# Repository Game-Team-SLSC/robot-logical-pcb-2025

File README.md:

# Game Team's robot pcb for Eurobot Junior 2025

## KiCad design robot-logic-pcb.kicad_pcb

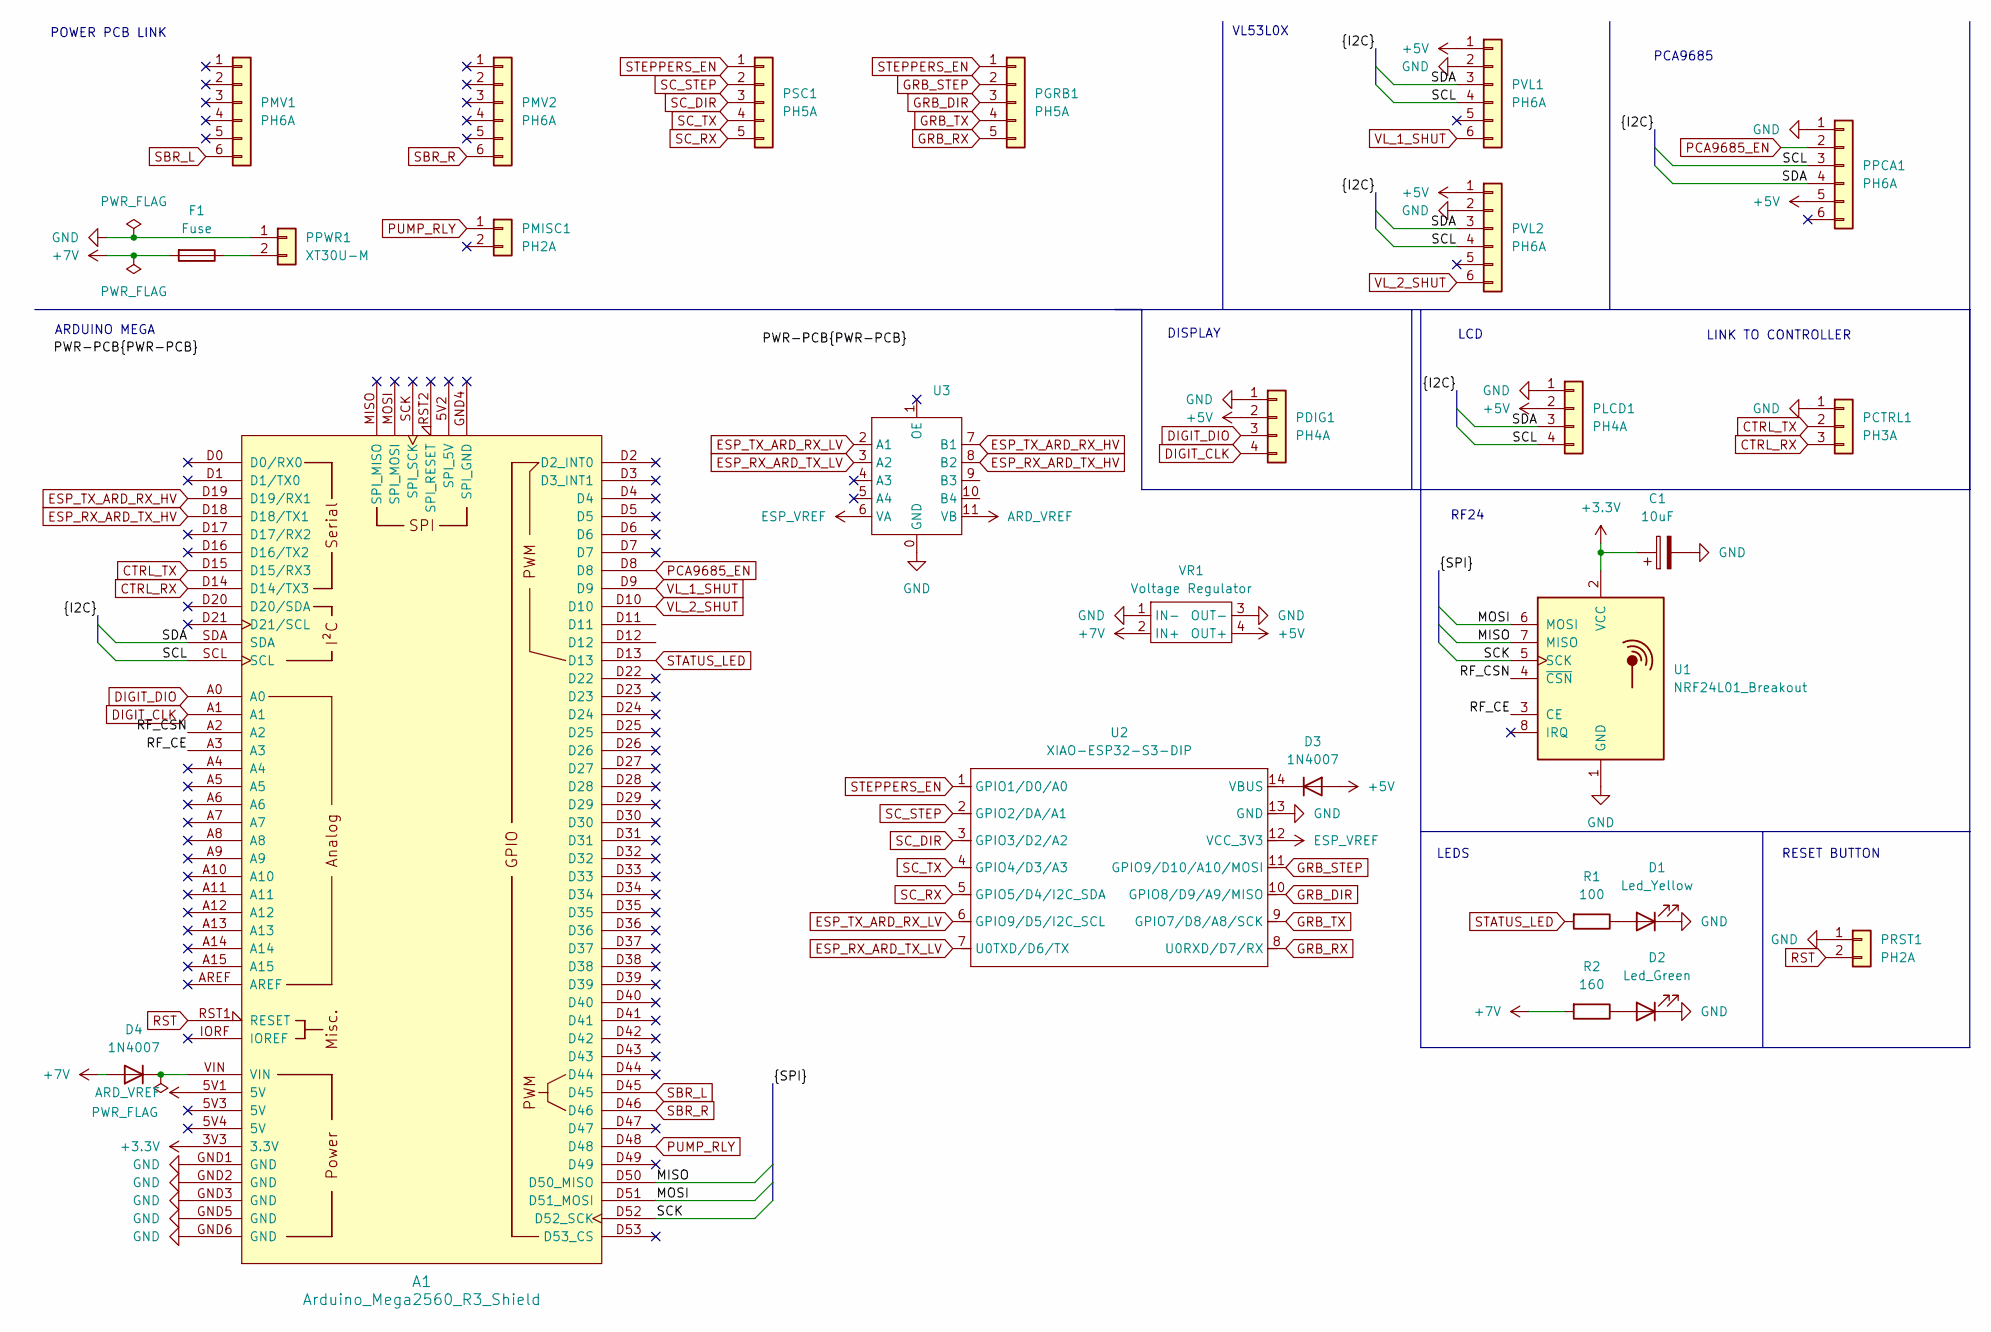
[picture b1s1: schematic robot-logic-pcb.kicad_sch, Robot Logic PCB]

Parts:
A1: Arduino_Mega2560_R3_Shield
C1: 10uF; CP_Radial_D5.0mm_P2.00mm
D1: Led_Yellow; LED_D5.0mm
D2: Led_Green; LED_D5.0mm
D3, D4: 1N4007; D_DO-41_SOD81_P2.54mm_Vertical_AnodeUp
F1: Fuse; Fuseholder_Cylinder-5x20mm_Schurter_0031_8201_Horizontal_Op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
PCTRL1: PH3A; JST_PH_B3B-PH-K_1x03_P2.00mm_Vertical
PDIG1: PH4A; JST_PH_B4B-PH-K_1x04_P2.00mm_Vertical
PGRB1: PH5A; JST_PH_B5B-PH-K_1x05_P2.00mm_Vertical
PLCD1: PH4A; JST_PH_B4B-PH-K_1x04_P2.00mm_Vertical
PMISC1: PH2A; JST_PH_B2B-PH-K_1x02_P2.00mm_Vertical
PMV1, PMV2: PH6A; JST_PH_B6B-PH-K_1x06_P2.00mm_Vertical
PPCA1: PH6A; JST_PH_B6B-PH-K_1x06_P2.00mm_Vertical
PPWR1: XT30U-M; AMASS_XT30U-M_1x02_P5.0mm_Vertical
PRST1: PH2A; JST_PH_B2B-PH-K_1x02_P2.00mm_Vertical
PSC1: PH5A; JST_PH_B5B-PH-K_1x05_P2.00mm_Vertical
PVL1, PVL2: PH6A; JST_PH_B6B-PH-K_1x06_P2.00mm_Vertical
R1: 100; R_Axial_DIN0207_L6.3mm_D2.5mm_P7.62mm_Horizontal
R2: 160; R_Axial_DIN0207_L6.3mm_D2.5mm_P7.62mm_Horizontal
U1: NRF24L01_Breakout; nRF24L01_Breakout
U2: XIAO-ESP32-S3-DIP; XIAO-ESP32S3-DIP
U3: TXB0104-BREAKOUT
VR1: Voltage Regulator; MP1584EN

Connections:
+3.3V: A1.3V3 (3.3V), C1.1, U1.2 (VCC)
+5V: D3.2 (A), PDIG1.2, PLCD1.2, PPCA1.5, PVL1.1, PVL2.1, VR1.4 (OUT+)
+7V: D4.2 (A), F1.2, R2.2, VR1.2 (IN+)
/MISO: A1.D50 (D50_MISO), U1.7 (MISO)
/MOSI: A1.D51 (D51_MOSI), U1.6 (MOSI)
/RF_CE: A1.A3, U1.3 (CE)
/RF_CSN: A1.A2, U1.4 (~CSN)
/SCK: A1.D52 (D52_SCK), U1.5 (SCK)
/SCL: A1.SCL, PLCD1.4, PPCA1.3, PVL1.4, PVL2.4
/SDA: A1.SDA, PLCD1.3, PPCA1.4, PVL1.3, PVL2.3
ARD_VREF: A1.5V1 (5V), U3.11 (VB)
CTRL_RX: A1.D14 (D14/TX3), PCTRL1.3
CTRL_TX: A1.D15 (D15/RX3), PCTRL1.2
DIGIT_CLK: A1.A1, PDIG1.4
DIGIT_DIO: A1.A0, PDIG1.3
ESP_RX_ARD_TX_HV: A1.D18 (D18/TX1), U3.8 (B2)
ESP_RX_ARD_TX_LV: U2.7 (U0TXD/D6/TX), U3.3 (A2)
ESP_TX_ARD_RX_HV: A1.D19 (D19/RX1), U3.7 (B1)
ESP_TX_ARD_RX_LV: U2.6 (GPIO9/D5/I2C_SCL), U3.2 (A1)
ESP_VREF: U2.12 (VCC_3V3), U3.6 (VA)
GND: A1.GND1 (GND), A1.GND2 (GND), A1.GND3 (GND), A1.GND5 (GND), A1.GND6 (GND), C1.2, D1.1 (K), D2.1 (K), PCTRL1.1, PDIG1.1, PLCD1.1, PPCA1.1, PPWR1.1, PRST1.1, PVL1.2, PVL2.2, U1.1 (GND), U2.13 (GND), U3.0 (GND), VR1.1 (IN-), VR1.3 (OUT-)
GRB_DIR: PGRB1.3, U2.10 (GPIO8/D9/A9/MISO)
GRB_RX: PGRB1.5, U2.8 (U0RXD/D7/RX)
GRB_STEP: PGRB1.2, U2.11 (GPIO9/D10/A10/MOSI)
GRB_TX: PGRB1.4, U2.9 (GPIO7/D8/A8/SCK)
unnamed: D1.2 (A), R1.1
unnamed: D2.2 (A), R2.1
unnamed: D3.1 (K), U2.14 (VBUS)
unnamed: A1.VIN, D4.1 (K)
unnamed: F1.1, PPWR1.2
PCA9685_EN: A1.D4, A1.D8, PPCA1.2
PUMP_RLY: A1.D48, PMISC1.1
RST: A1.RST1 (RESET), PRST1.2
SBR_L: A1.D45, PMV1.6
SBR_R: A1.D46, PMV2.6
SC_DIR: PSC1.3, U2.3 (GPIO3/D2/A2)
SC_RX: PSC1.5, U2.5 (GPIO5/D4/I2C_SDA)
SC_STEP: PSC1.2, U2.2 (GPIO2/DA/A1)
SC_TX: PSC1.4, U2.4 (GPIO4/D3/A3)
STATUS_LED: A1.D13, R1.2
STEPPERS_EN: PGRB1.1, PSC1.1, U2.1 (GPIO1/D0/A0)
VL_1_SHUT: A1.D9, PVL1.6
VL_2_SHUT: A1.D10, PVL2.6

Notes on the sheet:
LEDS
PCA9685
RESET BUTTON
ARDUINO MEGA
LCD
VL53L0X
LINK TO CONTROLLER
POWER PCB LINK
DISPLAY
RF24

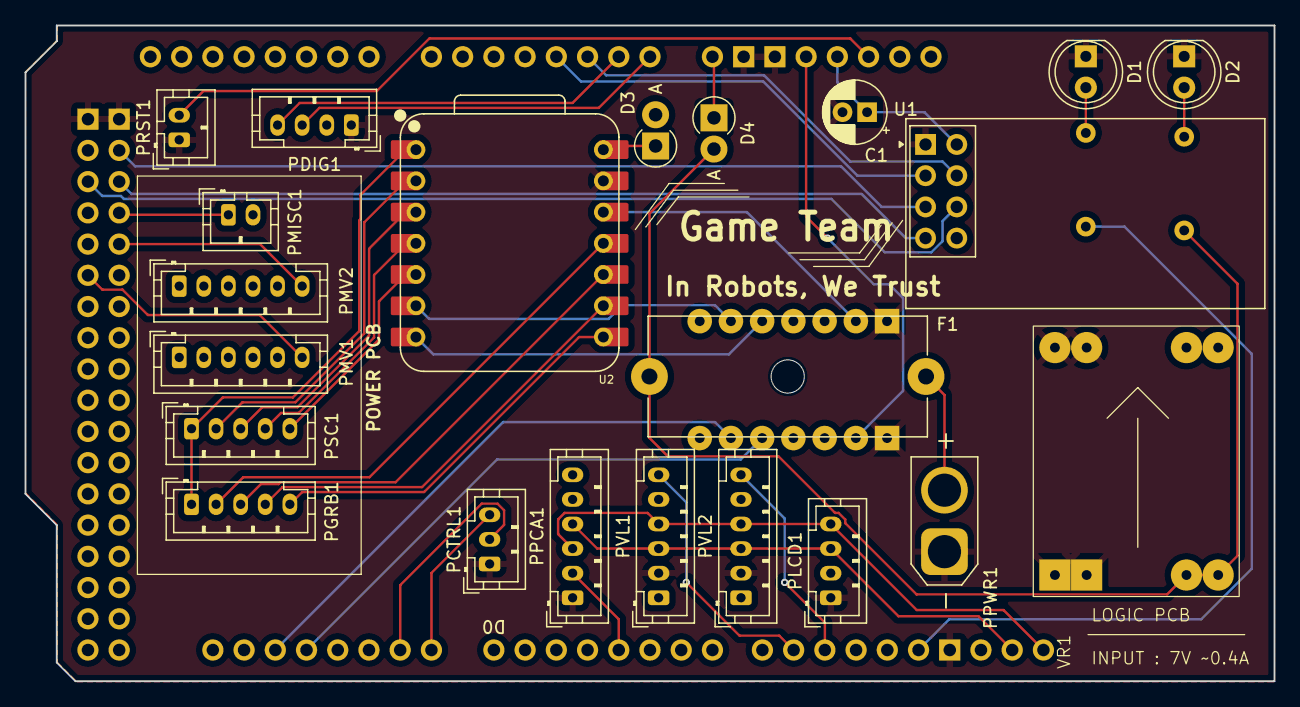
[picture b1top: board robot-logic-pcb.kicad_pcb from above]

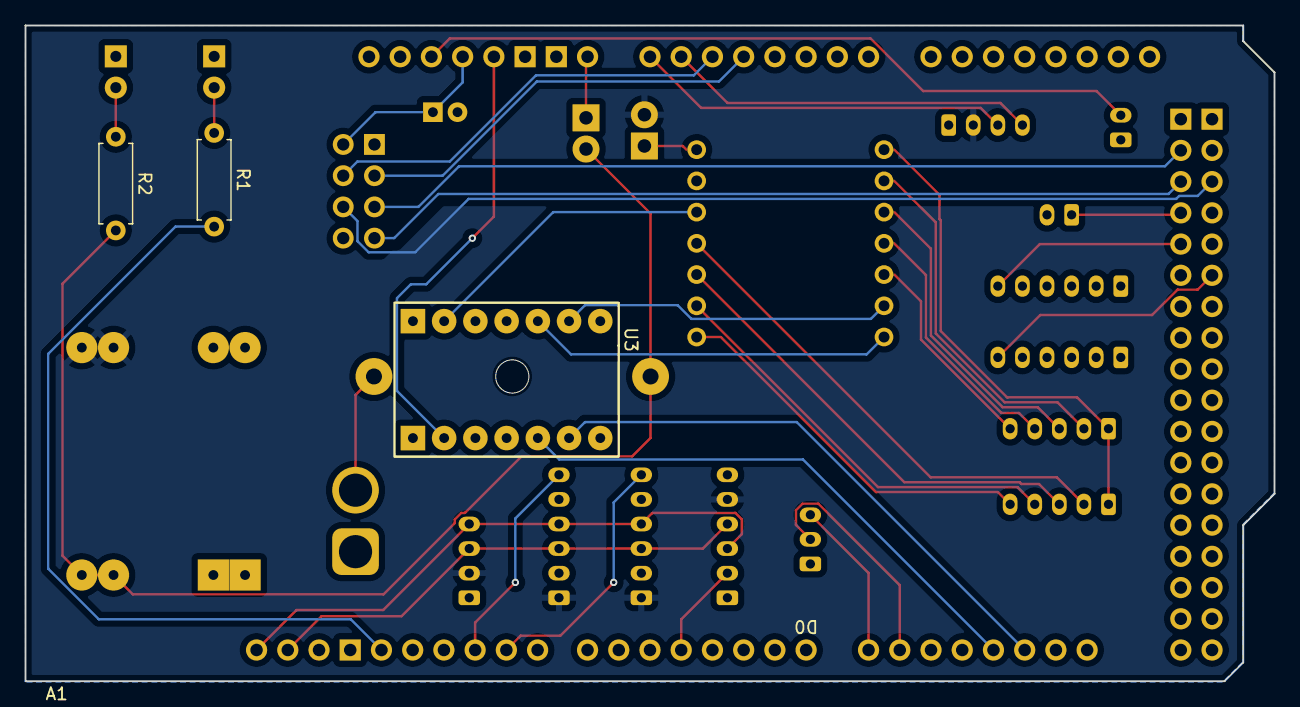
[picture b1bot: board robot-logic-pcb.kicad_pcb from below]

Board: 2 copper layers, 101.6 x 53.3 mm, 26 parts (3 on the bottom side), 43 nets.

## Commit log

2025-01-23 Add preview to readme
2025-01-23 Fix README.md
2025-03-13 remove fab and set gitignore
2025-03-13 Remove LFS for kicad files
2025-04-21 Post regionales Adds ESP32 for steppers and diodes to protect MCUs
2025-04-21 forgot to save sch lol
